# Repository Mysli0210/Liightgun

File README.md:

# Liightgun
Lightgun upgrade kit to utilize a wiimote camera and 4 IR points for screentracking.

The fusion 360 file, for the housing for 3 Ø5mm 940nm leds is located at https://a360.co/2tSsQLc so you can change it according to your needs. otherwise it is located as a stl file in the IR-point directory,

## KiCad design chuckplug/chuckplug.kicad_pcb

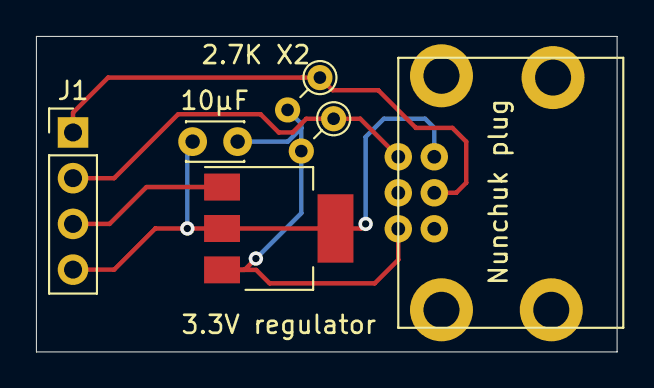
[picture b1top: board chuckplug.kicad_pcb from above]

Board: 2 copper layers, 32.3 x 17.5 mm, 6 parts (0 on the bottom side), 5 nets.

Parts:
2.7K X2: 2.7K; R_Axial_DIN0204_L3.6mm_D1.6mm_P2.54mm_Vertical
3.3V regulator: LF33_TO220; SOT-223
10µF: 10µF; C_Disc_D3.0mm_W2.0mm_P2.50mm
J1: Conn_01x04_Male; PinHeader_1x04_P2.54mm_Vertical
Nunchuk plug: Conn_01x06_Male; wiimote_plug
R2: 2.7K; R_Axial_DIN0204_L3.6mm_D1.6mm_P2.54mm_Vertical

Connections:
GND: 3.3V regulator.2, 3.3V regulator.4, 10µF.2, J1.4, Nunchuk plug.6
I2C_SCL: J1.1, Nunchuk plug.4, R2.1
I2C_SDA: 2.7K X2.1, J1.2, Nunchuk plug.5
unnamed: 2.7K X2.2, 3.3V regulator.3, 10µF.1, Nunchuk plug.1, R2.2
VCC: 3.3V regulator.1, J1.3

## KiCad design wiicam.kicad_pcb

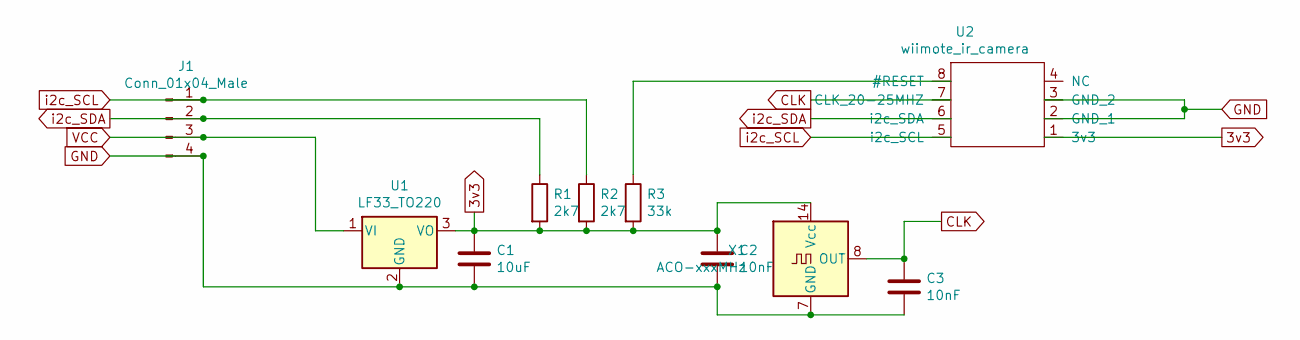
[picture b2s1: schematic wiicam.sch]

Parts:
C1: 10uF; C_Disc_D3.0mm_W1.6mm_P2.50mm
C2, C3: 10nF; C_Disc_D3.0mm_W1.6mm_P2.50mm
J1: Conn_01x04_Male; PinHeader_1x04_P2.54mm_Horizontal
R1, R2: 2k7; R_Axial_DIN0204_L3.6mm_D1.6mm_P2.54mm_Vertical
R3: 33k; R_Axial_DIN0204_L3.6mm_D1.6mm_P2.54mm_Vertical
U1: LF33_TO220; SOT-223
U2: wiimote_ir_camera; wii_ir_cam
X1: ACO-xxxMHz; Oscillator_DIP-14_LargePads

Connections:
3v3: C1.1, C2.1, R1.2, R2.2, R3.2, U1.3 (VO), U2.1 (3v3), X1.14 (Vcc)
CLK: C3.1, U2.7 (CLK_20-25MHZ), X1.8 (OUT)
GND: C1.2, C2.2, C3.2, J1.4, U1.2 (GND), U2.2 (GND_1), U2.3 (GND_2), X1.7 (GND)
unnamed: R3.1, U2.8 (#RESET)
VCC: J1.3, U1.1 (VI)
i2c_SCL: J1.1, R2.1, U2.5 (i2c_SCL)
i2c_SDA: J1.2, R1.1, U2.6 (i2c_SDA)

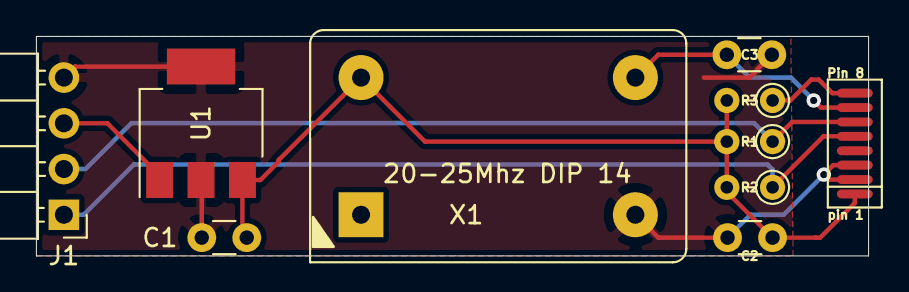
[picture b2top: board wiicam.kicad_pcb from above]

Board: 2 copper layers, 46.2 x 12.2 mm, 10 parts (0 on the bottom side), 7 nets.

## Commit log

2020-01-12 put kicad files for wiimote camera in folder

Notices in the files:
wiicam.kicad_pcb:
Creative Commons
Attr. - SA. 4.0
